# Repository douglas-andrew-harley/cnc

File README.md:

# FCCH CNC files

This repo contains archives of information related to the various CNC machines
at the Creator Hub. Each machine's data is in a separate top-level directory.
Within each directory, there are various sub-directories for hardware design,
software config files, etc.

## Wood-48x48

CNC Router in wood shop.

## Metal_mill

Donated 3-axis mill previously retrofitted for CNC.  The controller was old and did not work with LinuxCNC and it also was just mounted on a plate and not enclosed so we built a new controller modelled after the Wood-48x48 controller.  This folder contains the design and documentation for that new controller cabinet.

[metal_mill README](metal_mill/README.md)

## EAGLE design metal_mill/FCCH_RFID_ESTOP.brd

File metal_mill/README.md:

# Metal Mill CNC Controller

This project is a CNC controller for a mill or other 3 axis machaine that uses 35V-40V DC servo motors.

It consists of 2 parts

1) a controller cabinet that controls the motors in accordance to instructions from a computer running LinuxCNC and
2) an RFID and E-Stop module that connects to the controller cabinet to controll whether the servo drives are enabled.

Design File PDFs

* [metal_mill_wiring.sch (pdf)](metal_mill_wiring.pdf) (created in EagleCAD)
* [FCCH_RFID_ESTOP.sch (pdf)](FCCH_RFID_ESTOP.sch.pdf) (created in EagleCAD)
* [FCCH_RFID_ESTOP.brd (pdf)](FCCH_RFID_ESTOP.brd.pdf) (created in EagleCAD)
* [FCCH_RFID_ESTOP.brd (fab print pdf)](FCCH_RFID_ESTOP.brd.fab.pdf) (created in EagleCAD)
* [panel_cutouts.FCStd (pdf)](panel_cutouts.pdf) (created in FreeCAD)

## Controller Cabinet Components

* (1) 7i96s Controller
* (3) G320X - Gecko DC Servo Drive
* (1) NSP-1600-36 Power Supply
* (1) 12V to 5V buck Converter
* (4) Panel mount GX16-8 Aviation Connectors
* (6) Panel mount 3.5mm mono jacks with plug detection (3 terminal)
* (1) Panel mount A/C C-14 reciptical
* (3) Power Bus Bars (at least 5 position)
* (1) case (we are using a salvaged desktop PC)
* (1) panel for connectors

### 7i96s Controller

This is a card that provides IO and axis drive output for LinuxCNC.  The card connects to a PC via a point to point (no switch) dedicated Ethernet.  This project describes how the inputs and outputs of the 7i96s should be connected to interface with the mill.

Input Summary

* INPUT0: Drive Power OK<br>
  High (3.5 ~ 5.5V) : When the Vout ≦ 77% ± 5%.<br>
  Low (-0.5 ~ 0.5V) : When Vout ≧ 80% ± 5%.
* INPUT1: Drive Power T-Alarm<br>
  High (3.5 ~ 5.5V) : When the internal temperature exceeds the limit of temperature alarm, or when Fan fails.<br>
  Low (-0.5 ~ 0.5V) : When the internal temperature is normal, and when Fan normally works.
* INPUT2: Xmin limit switch (normally open)
* INPUT3: Xmax limit switch (normally open)
* INPUT4: Ymin limit switch (normally open)
* INPUT5: Ymax limit switch (normally open)
* INPUT6: Zmin limit switch (normally open)
* INPUT7: Zmax limit switch (normally open)
* INPUT8: X drive OK/Fault High==OK
* INPUT9: Y drive OK/Fault High==OK
* INPUT10: Z drive OK/Fault High==OK
* IN_COM: +5V (all inputs will be 0-5V)

Output Summary

* OUT0: Reset Drivers. Hold high for at least 1 sec to reset X,Y, and Z drivers to clear a fault on any or all drivers. INPUTs 8,9,10 read the OK/fault state of the X,Y,Z drivers respectively.
* OUT1: Motor Power Enable.
* Stepper Drive Units 0-2 connect to the 3 G320X drivers

### G320X - Gecko DC Servo Drive

The 7i96s provides stepper motor outputs for the drives but the mill we are using has DC servo motors installed.  The G320X provides translation between the stepper motor signals and DC servo motor control. Each servo motor connects to a G320X via 2 dc power wires and 4 encoder wires. The encoder provides feedback to the G320X so that it can determine what power to send to the motor to make its position match the position specified by LinuxCNC.

The G320X drives the motors with a PID controll. There are three screw pots to adjust the position, integral, and derivated gains. When the mill is operational, each axis needs to be tuned to minimize the error.

<https://www.youtube.com/watch?v=Ic4CvIOm6O4>

### NSP-1600-36 Power Supply

This PS provides up to 500W to each of the X,Y,Z drives at an adjustable voltage between 35V and 40V. The mill's X axis motor is rated at 38V and the Y axis is rated at 40V so we can adjust the voltage to 39V to split the difference. The Z axis motor is not easily accessible so we assume its either 38 or 40V. 

The main power can be turned on and off independent of the allways on aux power (12V@850ma) which we use to power all the components in the cabinet and the E-Stop RFID module.

The PS has a 16 pin connector that provides the aux power and control signals which we interface through the 7i96s so that Linux CNC can controll if the drive power is on or off and determine its status.

### 12V to 5V buck Converter

The aux power from the NSP-1600-36 is 12V but the 7i96s requires 5V.

### Panel mount GX16-8 Aviation Connectors

Each axis motor is connected to the controller cabinet via a GX16-8 Aviation connector. These connectors are panel mount and screw on for a secure connection. They are avaiable with even number of connectors. We need 7 so we got the 8 conductor. 

We terminate two separate cables into the GX16-8

1) 14 gauge 2 conductor cable for motor power A 38V@500W motor can draw up to 12.5A which requires 14 gauge wires for the 2 motor power wires. 
2) 22 gauge 5 conductor cable for the motor encoder signals and a separate motor housing ground wire. The encoder on these motors use single ended singles so require 4 wires. Since the encoders are single ended (not differential), the encoder cables should be shielded with the shield connected to the case ground on the cabinet side and left unconnected on the motor side. The encoder cable should also have a 5th conductor which is connected to the power supply ground in the cobinet and to the motor housing.

### Panel mount 3.5mm mono jacks with plug in detection

The limit switches are connected to the controller cabinet via 3.5mm mono plugs/jacks. 3 terminal jacks are used where the third terminal makes contact with the tip terminal when no jack is inserted. This is used so that when the jack is removed, it will complete the circuit as if the limit switch was activated. This makes it so that if a limit switch is removed, LinuxCNC will think that the limit switch is tripped and will not drive the machine in that direction. 

### Panel mount A/C C-14 reciptical

This is a stanard reciptical for connecting a device to building power.

### Power Bus Bars

To be sourced...

To connect components to GND, +5V and +12V, we use 3 bus bars that can terminate bare wire leads.

### Case

We are using an old desktop PC from a thrift store.  An alarm panel case or similar would also be suitable.

### Panel for connectors

The file [panel_cutouts.FCStd](panel_cutouts.pdf) (created with FreeCAD) documents the panel cutouts to accept the various panel mount jacks the cabinet uses to connect to the motors, limit switches, FCCH_RFID_ESTOP_module, power, and Ethernet to the computer running LinuxCNC

## Controller Cabinet Cable Harnesses

Inside the controller cabinet, all components are connected via the following wire harnesses. The Wn label of each harness refers to the designation in the schematic.

The schematic [metal_mill_wiring.sch (pdf)](metal_mill_wiring.pdf) (created in EagleCAD) documents the connections.

### Cables required

* 22 gauge 6 conductor cable
* 22 gauge 4 conductor cable
* 22 gauge 2 conductor cable
* 22 gauge single black wire
* 18 gauge 2 conductor red/black
* 18 gauge 3 conductor red/orange/black
* 14 gauge 2 conductor red/black
* 14 gauge 3 conductor line cord

### (W1) Stepper and reset cables from 7i96s to each of the G320X servo drives

3 needed
bare leads to bare leads

* 22 gauge 4 conductor cable
  * one end: bare leads into the terminals on the G320X's
    * cable shield: no connection (only connect on other end)
    * black:  COM
    * blue:   STEP
    * yellow: DIR
    * orange: ERR/RES
  * other end: bare leads into the 7i96s TB3 and TB3 terminals (see schematic)
    * cable shield: connect to chassis ground screw located near the 7i96s
    * black:  TB1 GND(n)
    * blue:   TB1 STEP(n)+
    * yellow: TB1 DIR(n)+
    * orange: TB3 INPUT8 (ERR/RES input)

Build Notes:

We used a shielded 8 conductor wire because the maker space had a big spool of it. The 4 unused conductors were cut short and sealed under a short piece of heat shrink.

On the 7i96s end, the orange and shield wires need to be about 4 inches longer than the others because they go to different places. Strip 5 inches of the cable insulation. cut black,blue,yellow wires to about 1.25 inches. Heat shrink a 3/8 inch tube so that half is over the insulation and half is over the protrubing wires. 

On the G320X end, the orange wire needs to be longer than the others by about an inch. Strip a little over 2 inches of insulation. Cut the shield wire short to the insulation (wont be connected on this end). Cut the black,blue, and yellow wires to about an inch. Heat shrink about 3/8 inch tube over the insulation and wires.

### (W2) Motor Power and Encoder Jacks

3 needed
GX16-8 Aviation connector to 3 separate cables with bare leads

* 14 gauge 2 conductor red/black
  * one end: solder to GX16-8
    * black: terminal 1
    * red:   terminal 2
  * other end: bare leads screw into G320X terminals
    * black: arm-
    * red:   arm+
* 22 gauge 4 conductor cable
  * one end: solder to GX16-8
    * C1: terminal 4
    * C2: terminal 5
    * C3: terminal 6
    * C4: terminal 7
  * other end: bare leads to G320X screw terminals
    * C1: ENC_GND
    * C2: ENC_5VDC
    * C3: Channel_A
    * C4: Channel_B
* 22 gauge single black wire
  * one end: solder to GX16-8
    * terminal 8
  * other end connects to the 9 position gnd bus bar located near the panel

### (W3) E-Stop and RFID Module Jacks

1 needed
GX16-8 Aviation connector to 2 separate cables

* 18 gauge 3 conductor red/orange/black
  * one end: solder to GX16-8
    * black:  terminal 1
    * red:    terminal 2
    * orange: terminal 3
  * other end: bare leads to GND,+5V, and +12V bus bars
* 22 gauge 6 conductor cable
  * one end: solder to GX16-8
    * C1: terminal 4
    * C2: terminal 5
    * C3: terminal 6
    * C4: terminal 7
    * C5: terminal 8
    * C6: N/C

### (W4) Limit Switch Panel Mount Jacks

1 needed
6x 3.5 mono panel mount jacks to 6x ground wires and 1x 6 conductor cables with bare leads

* 6x 22 gauge single black wire connects each jack terminal 1 and 2 and then to the 9 position gnd bus bar located near the panel.
* 1x 22 gauge 6 conductor cable
  * one end: solder to terminal 3 on each jack
  * other end: bare leads connect to 7i96s screw terminals
    * Xmin: TB3.3 (INPUT2)
    * Xmax: TB3.4 (INPUT3)
    * Ymin: TB3.5 (INPUT4)
    * Ymax: TB3.6 (INPUT5)
    * Zmin: TB3.7 (INPUT6)
    * Zmax: TB3.8 (INPUT7)

### (W5) Servo Driver Power

1 needed
2 circular lug crimp connectors to 3x 2 conductor cables with bare leads

* 3x 14 gauge 2 conductor red/black
  * one end collect the 3 red wires together into a circular crimp lug connector. do the same with the balck cables. The two circular connects will be bolted to the main PS lugs
  * other ends of the 3 cables has bare leads to screw into the PWR_GND (black) and 18V_to 80V_PWR terminal of the 3 G320X servo drivers

### (W6) A/C Input to PS

1 needed
crimp spade connectors to crimp spade connectors

* 14 gauge 3 conductor line cord

### (W7) Power Supply signals

1 needed
HRS DF11-16DS 16 pin IDC to bare leads

* 18 gauge 2 conductor red/black
  * one end: IDC pins inserted in 16x connector
    * red  : pin 1
    * black: pin 2
  * other end: bare leads to GND and 12V bus bars
* 22 gauge 4 conductor cable
  * one end: IDC pins inserted in 16x connector
    * C1: pin 3
    * C2: pin 4
    * C3: pin 5
    * C4: pin 6
  * other end: bare leads screwed into 7i96s terminals
    * C1: TB3-16 (OUT1+)
    * C2: TB3-15 (OUT1-)
    * C3: TB3-1  (INPUT0)
    * C4: TB3-2  (INPUT1)

Note that the DF11-16DS connector on the PS has 16 positions. 1-6 are connected as above. In addition, two loop back wires on the connector are needed to connect positions 13 to 15, and 14 to 16. The PS came with a connector that had these loop back wires already installed. These loopback wires implement the local voltage sensing as described in the datasheet. If we ever want to implement remote sensing to compensate for drops seen at the motors, we would replace theses loopbacks with wires connecting 15 and 16 to the + and - motor leads.

### (W8) 7i96s Power

1 needed
bare leads to bare leads

* 18 gauge 2 conductor red/black

## E-Stop and RFID Module (FCCH_RFID_ESTOP)

This is a custom PCB in a separate enclosure that can be mounted in a accessible location on the mill for the operator to interact with. The enclosure contains this custom PCB and also the FCCH RFID PCB. An 8 pin GX16-8 Aviation connector connects this enclosure with the controller cabinet.

The FCCH_RFID_ESTOP module provides two functions.

1) RFID Authorization. Major machines at the FCCH (fort Collins Creator Hub) have RFID based access control. When an authorized RFID tag is not present in the V slot of this module, the axis motors are inhibited.
2) E-Stop switch. If the E-Stop is pressed, the axis motors are inhibited.

The ERR/RES lines of the G320X drivers are brought to this module. They are attached to ground (which inhibits the drivers) through the normally closed contacts of a safety relay. When both a valid RFID tag is present and the E-Stop switch is not active, the relay is energized, breaking the connection to ground and enabling the drivers.

The file [FCCH_RFID_ESTOP.sch (pdf)](FCCH_RFID_ESTOP.sch.pdf) contains the schematic for the custom PCB and [FCCH_RFID_ESTOP.brd (pdf)](FCCH_RFID_ESTOP.brd.pdf) is the board layout.

For physical dimensions of the board refer to [FCCH_RFID_ESTOP.brd.fab.pdf](FCCH_RFID_ESTOP.brd.fab.pdf)

## FCCH_RFID_ESTOP Cable Harnesses

### (EW1) GX16-8 connector to FCCH_RFID_ESTOP board

1 needed
GX16-8 panel mount side to bare leads

* Ethernet cable soldered to the panel mount. Wires connected per schematic to screw terminals of the FCCH_RFID_ESTOP board.

### (EW2) FCCH_RFID_ESTOP board to FCCH_RFID board

1 needed
bare leads to bare leads

* 22 gauge 4 conductor cable

### (EW3) Controller Cabinet to FCCH_RFID_ESTOP module

1 needed
GX16-8 to GX16-8

Ethernet cable soldered to the free hanging side of the GX16-8 connects. All pins pass through straight.

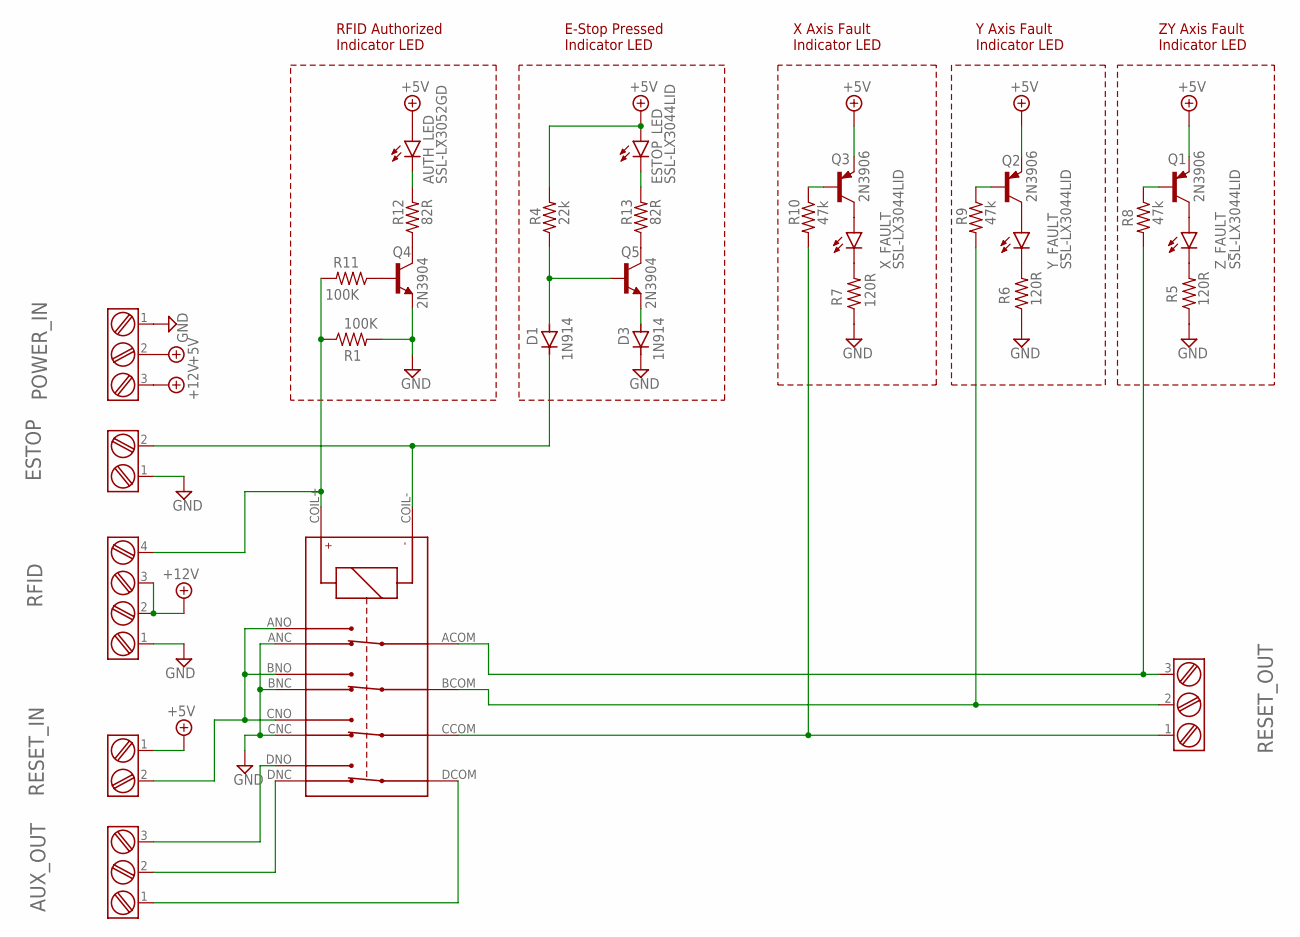
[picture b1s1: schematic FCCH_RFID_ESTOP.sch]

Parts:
AUTH_LED: SSL-LX3052GD; LED3MM
AUX_OUT: EURO-CON-3_2.54P; CONN3-2.54P
D1, D3: 1N914; D-5
ESTOP: EURO-CON-2_2.54P; CONN2_2.54P
ESTOP_LED: SSL-LX3044LID; LED3MM
POWER_IN: EURO-CON-3_2.54P; CONN3-2.54P
Q1, Q2, Q3: 2N3906; TO92
Q4, Q5: 2N3904; TO92
R1, R11: 100K; 0204/7
R4: 22k; 0204/7
R5, R6, R7: 120R; 0204/7
R8, R9, R10: 47k; 0204/7
R12, R13: 82R; 0204/7
RESET_IN: EURO-CON-2_2.54P; CONN2_2.54P
RESET_OUT: EURO-CON-3_2.54P; CONN3-2.54P
RFID: EURO-CON-4_2.54P; CONN4-2.54P
U$1: NC4D-JP-DC5V; NC4D-JP
X_FAULT: SSL-LX3044LID; LED3MM
Y_FAULT: SSL-LX3044LID; LED3MM
Z_FAULT: SSL-LX3044LID; LED3MM

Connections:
+5V: AUTH_LED.A, ESTOP_LED.A, POWER_IN.2, Q1.3 (E), Q2.3 (E), Q3.3 (E), R4.2, RESET_IN.1
+12V: POWER_IN.3, RFID.2, RFID.3
AUX_RELAY_COM: AUX_OUT.1, U$1.DCOM
AUX_RELAY_NC: AUX_OUT.2, U$1.DNC
AUX_RELAY_NO: AUX_OUT.3, U$1.DNO
ESTOP: D1.C, ESTOP.2, U$1.COIL-
GND: D3.C, ESTOP.1, POWER_IN.1, Q4.3 (E), R1.2, R5.1, R6.1, R7.1, RFID.1, U$1.ANC, U$1.BNC, U$1.CNC
unnamed: R7.2, X_FAULT.K (C)
unnamed: RESET_IN.2, U$1.ANO, U$1.BNO, U$1.CNO
unnamed: Q4.1 (C), R12.1
unnamed: Q4.2 (B), R11.1
unnamed: D1.A, Q5.2 (B), R4.1
unnamed: Q5.1 (C), R13.1
unnamed: D3.A, Q5.3 (E)
unnamed: Q3.1 (C), X_FAULT.A
unnamed: R6.2, Y_FAULT.K (C)
unnamed: Q2.1 (C), Y_FAULT.A
unnamed: R5.2, Z_FAULT.K (C)
unnamed: Q1.1 (C), Z_FAULT.A
unnamed: ESTOP_LED.K (C), R13.2
unnamed: Q3.2 (B), R10.1
unnamed: AUTH_LED.K (C), R12.2
unnamed: Q2.2 (B), R9.1
unnamed: Q1.2 (B), R8.1
RFID_ENABLE: R1.1, R11.2, RFID.4, U$1.COIL+
X_ERR/RES: R10.2, RESET_OUT.1, U$1.CCOM
Y_ERR/RES: R9.2, RESET_OUT.2, U$1.BCOM
Z_ERR/RES: R8.2, RESET_OUT.3, U$1.ACOM

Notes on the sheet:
E-Stop Pressed Indicator LED
RFID Authorized Indicator LED
X Axis Fault Indicator LED
Y Axis Fault Indicator LED
ZY Axis Fault Indicator LED

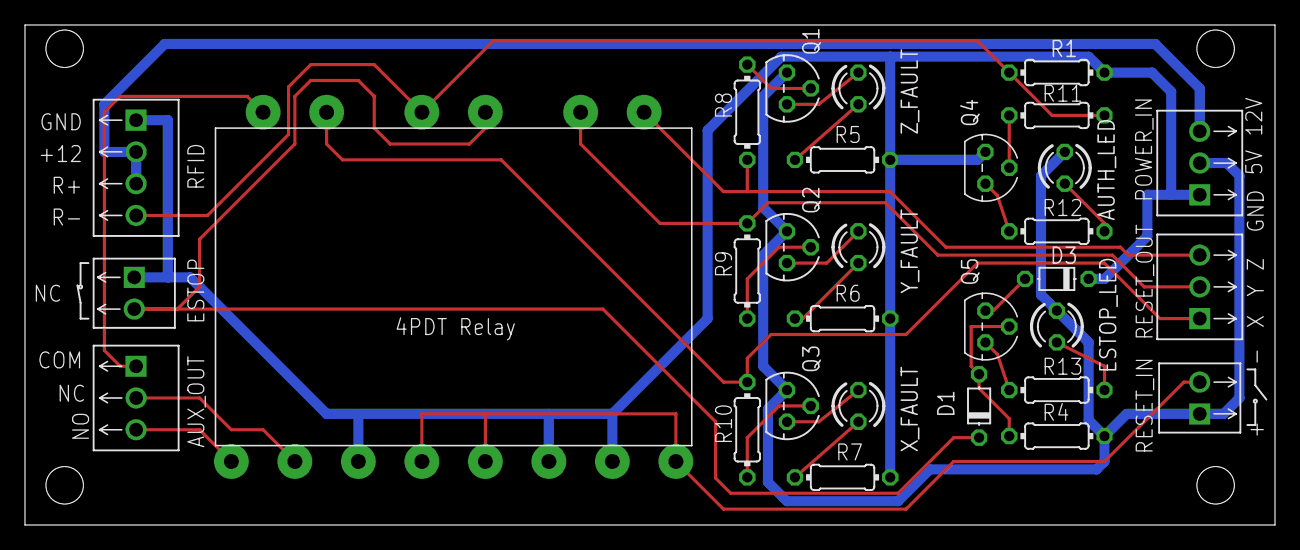
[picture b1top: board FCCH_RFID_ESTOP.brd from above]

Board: 2 copper layers, 100.0 x 40.0 mm, 30 parts (0 on the bottom side), 28 nets.

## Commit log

2024-03-31 initial commit of metal_mill project folder
2024-04-04 First fully documented commit. Some details like the FCCH_RFID_ESTOP board layout still need to be done.
2024-04-04 added pdf's so that people can review the schematics without having EagleCAD
2024-04-04 metal_mill: changed schematic and CAD file links in the README.md to open the corresponding pdf files to make it easier to browse the project
2024-04-07 Added FCCH_RFID_ESTOP board layout and wire harnesses description in README.md
2024-04-15 check point: before changing the reset relay to allow +5V as well as ground
2024-04-15 * changed reset_in to use the NO contacts of the relay * grouped the screw terminals that will connect to the GX16-8
2024-04-15 updated FCCH_RFID_ESTOP pdf's
2024-04-20 fixed some mistakes found by prototyping on a breadboard. * moved wire terminals to the end of the board * updated LED devices (was using a header) * updated resistor values
